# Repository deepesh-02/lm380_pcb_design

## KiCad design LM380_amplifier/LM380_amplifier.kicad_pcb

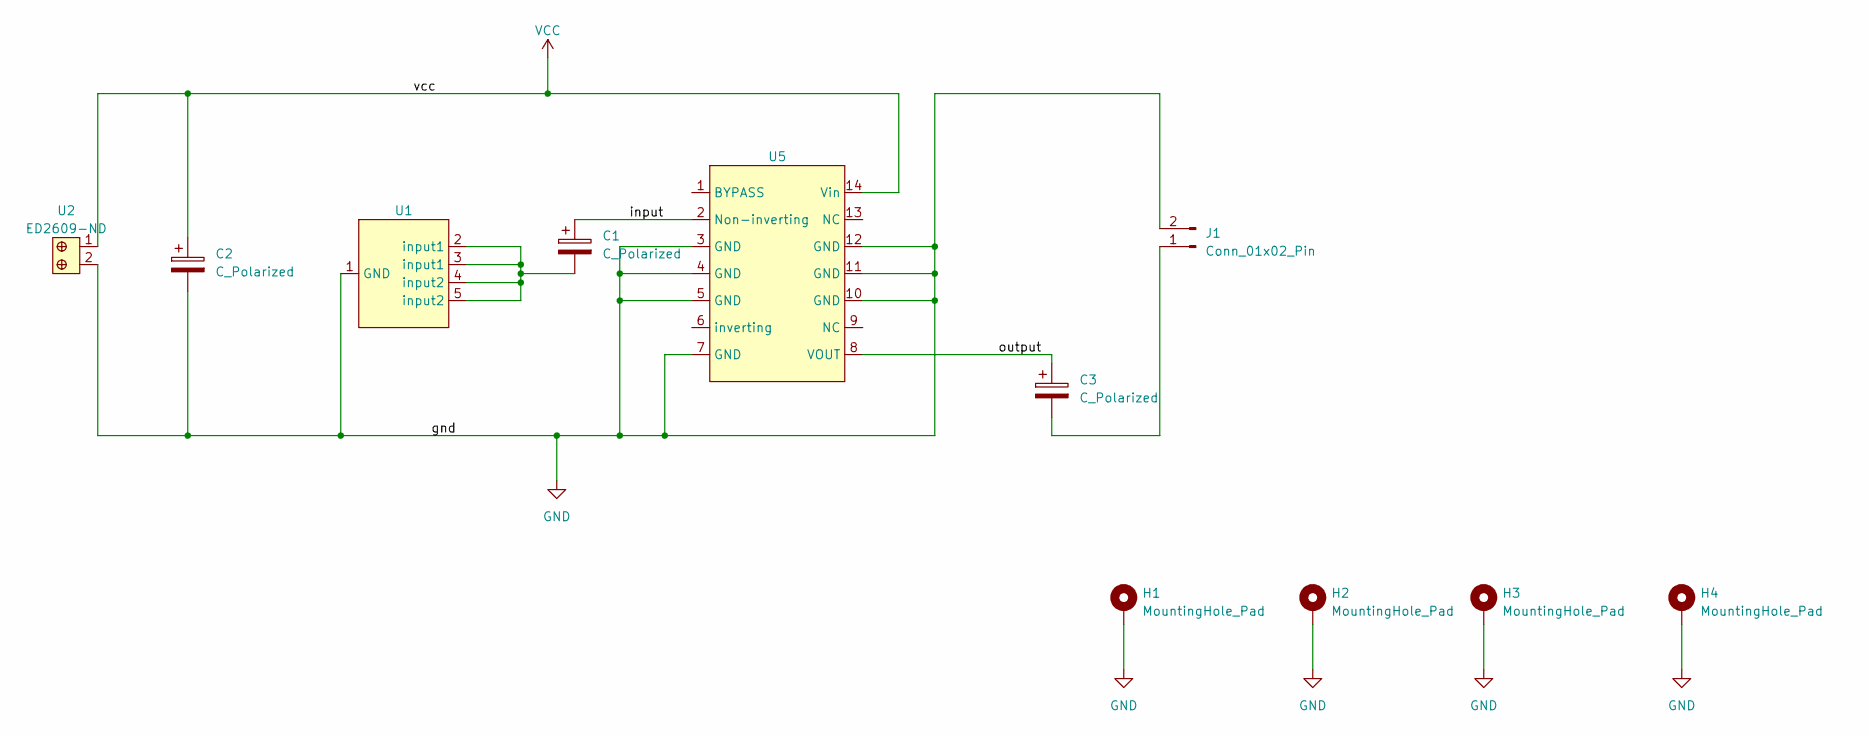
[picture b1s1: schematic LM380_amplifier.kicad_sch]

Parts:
C1: C_Polarized; CP_Radial_D5.0mm_P2.50mm
C2, C3: C_Polarized; CP_Radial_D10.0mm_P5.00mm
H1, H2, H3, H4: MountingHole_Pad; MountingHole_2.5mm_Pad
J1: Conn_01x02_Pin; JST_XH_B2B-XH-A_1x02_P2.50mm_Vertical
U1: 3.5mm_PJ324-M
U2: ED2609-ND; TerminalBlock_bornier-2_P5.08mm
U5: LM380_custom

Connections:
/input: C1.1, U5.2 (Non-inverting)
/output: C3.1, U5.8 (VOUT)
GND: C2.2, H1.1, H2.1, H3.1, H4.1, J1.2, U1.1 (GND), U2.2, U5.3 (GND), U5.4 (GND), U5.5 (GND), U5.7 (GND), U5.10 (GND), U5.11 (GND), U5.12 (GND)
unnamed: C1.2, U1.2 (input1), U1.3 (input1), U1.4 (input2), U1.5 (input2)
unnamed: C3.2, J1.1
VCC: C2.1, U2.1, U5.14 (Vin)

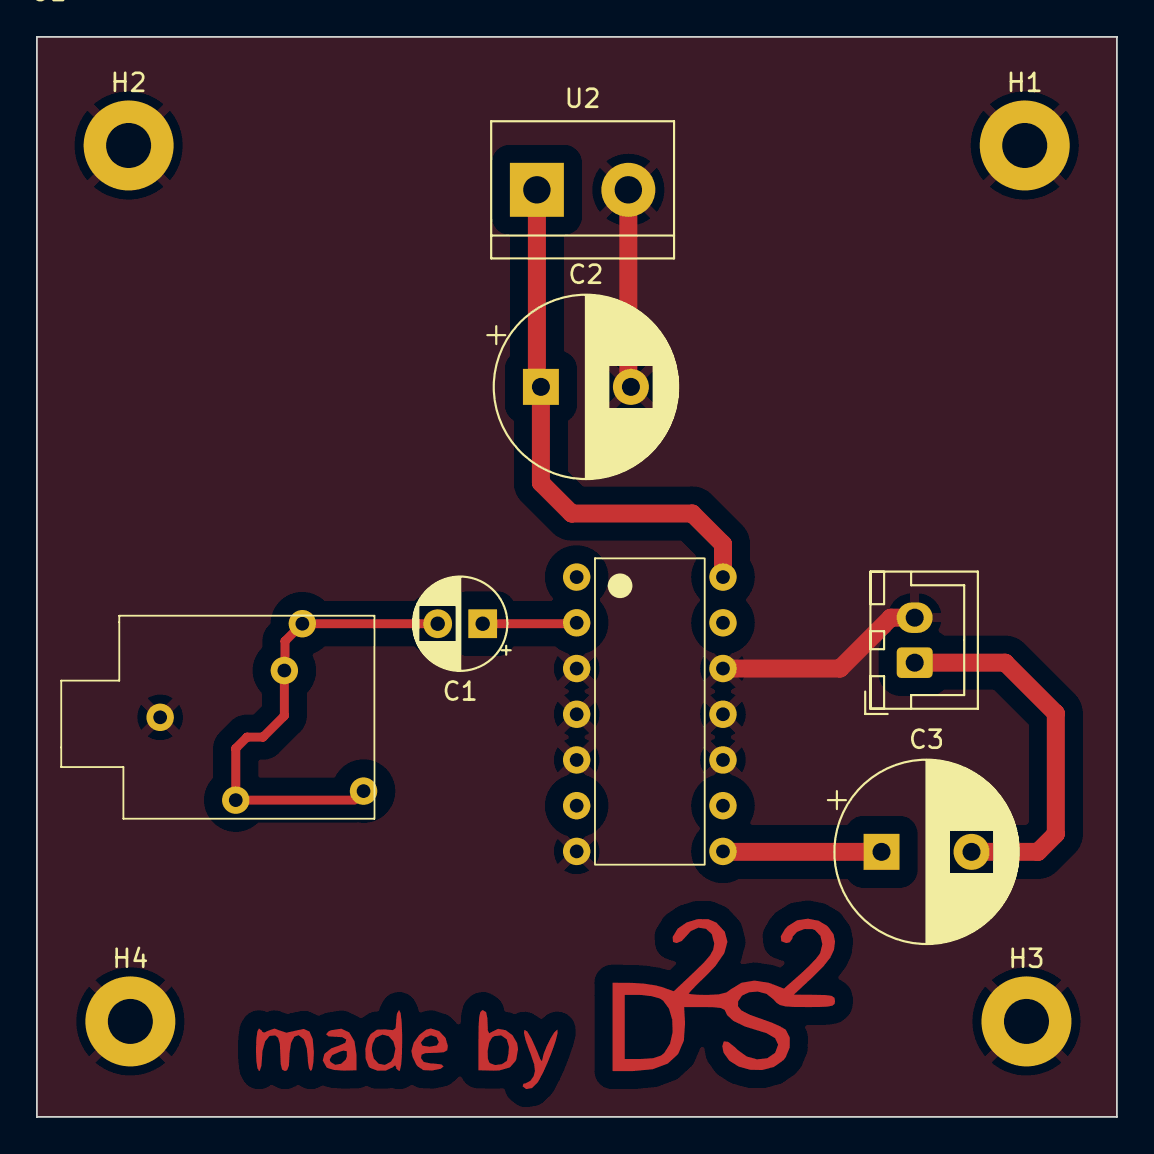
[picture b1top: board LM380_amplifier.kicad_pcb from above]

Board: 2 copper layers, 60.0 x 60.0 mm, 11 parts (0 on the bottom side), 6 nets.

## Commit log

2023-05-08 added pcb files
